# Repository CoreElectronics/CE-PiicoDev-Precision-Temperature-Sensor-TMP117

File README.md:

# PiicoDev® Precision Temperature Sensor TMP117

This is the repo for the Core Electronics [PiicoDev Precision Temperature Sensor TMP117](https://core-electronics.com.au/catalog/product/view/sku/CE07502).

The PiicoDev Precision Temperature Sensor features a low-power, high precision TMP117 with 16-bit resolution and an accuracy of ±0.1°C (across -20°C to +50°C) with no calibration required. The full operating range is -55°C to +150°C.

- Small size, high accuracy
- PiicoDev connector, compatible with Qwiic and STEMMA QT (3.3V only)
- 2.54mm breakout for breadboarding/prototyping
- Manufactured and [supported](https://core-electronics.com.au/contacts/) in Australia by Core Electronics

**Technical Specifications:**

- 4 configurable I2C addresses. Default: 0x48
- Dimensions: 25.4x25.4mm
- Mounting Holes: 2x M2.5
- TMP117:
  - ±0.1°C from -20°C to +50°C
  - ±0.15°C from -40°C to +70°C
  - ±0.2°C from -40°C to +100°C
  - ±0.25°C from -55°C to +125°C
  - ±0.3°C from -55°C to +150°C
  - 0.0078°C resolution (1 LSB)

# License
This project is open source - please review the LICENSE.md file for further licensing information.

If you have any technical questions, or concerns about licensing, please contact technical support on the [Core Electronics forums](https://forum.core-electronics.com.au/).

# Attribution
The hardware design of this module is influenced by the design from [Sparkfun](https://github.com/sparkfun/SparkFun_High_Precision_Temperature_Sensor_TMP117_Qwiic).

*\"PiicoDev\" and the PiicoDev logo are trademarks of Core Electronics Pty Ltd.*

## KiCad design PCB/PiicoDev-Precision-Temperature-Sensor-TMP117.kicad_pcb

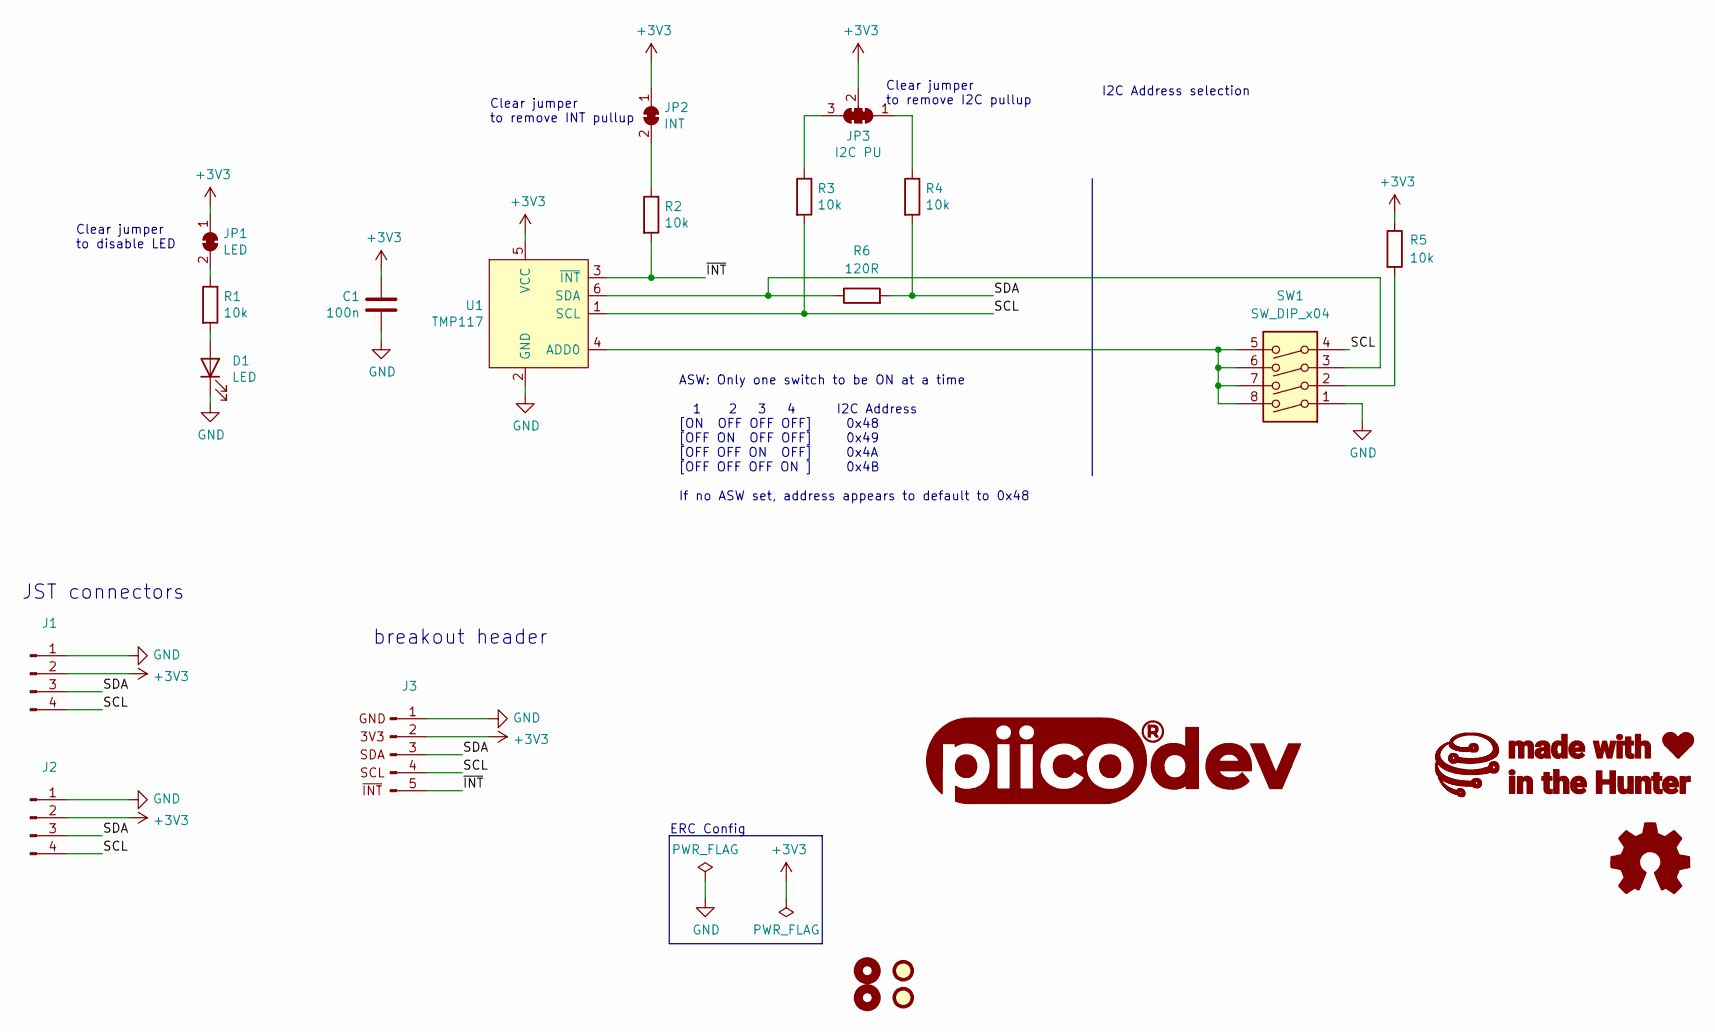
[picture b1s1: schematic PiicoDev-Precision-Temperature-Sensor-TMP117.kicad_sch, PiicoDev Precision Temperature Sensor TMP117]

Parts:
C1: 100n; C_0402_1005Metric
D1: LED; LED_0603_1608Metric
FID1, FID2: Fiducial; Fiducial_1mm_Mask2mm
G1: LOGO_CoreElectronics_no-text; CoreElectronics_logo_5mm
G2: LOGO_piico; piicodev_logo_14.2x3.4mm
G3: LOGO_made-with-love; piicodev_logo_14.2x3.4mm
H1, H4: MountingHole; MountingHole_2.7mm_M2.5
J1, J2: JST_SH_SM04B-SRSS-TB_1x04-1MP_P1.00mm_Horizontal
J3: PiicoDev_header_5pin_INT
JP1: LED; SolderJumper-2_P1.3mm_Bridged_RoundedPad1.0x1.5mm
JP2: INT; SolderJumper-2_P1.3mm_Bridged_RoundedPad1.0x1.5mm
JP3: I2C PU; SolderJumper-3_P1.3mm_Closed_RoundedPad1.0x1.5mm_NumberLabe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
LOGO1: Logo_Open_Hardware_Small; oshw
R1, R2, R3, R4, R5: 10k; R_0402_1005Metric
R6: 120R; R_0402_1005Metric
SW1: SW_DIP_x04; SW_DIP_x04_Slide_CHS-04A1
U1: TMP117; WSON-6-1EP_2x2mm_P0.65mm_EP1x1.6mm

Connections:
+3V3: C1.2, J1.2, J2.2, J3.2, JP1.1 (A), JP2.1 (A), JP3.2 (C), R5.1, U1.5 (VCC)
/SCL: J1.4, J2.4, J3.4, R3.2, SW1.4, U1.1 (SCL)
/SDA: J1.3, J2.3, J3.3, R4.2, R6.2
/~INT: J3.5, R2.2, U1.3 (~INT)
GND: C1.1, D1.1 (K), J1.1, J2.1, J3.1, SW1.1, U1.2 (GND)
unnamed: D1.2 (A), R1.2
unnamed: JP1.2 (B), R1.1
unnamed: JP2.2 (B), R2.1
unnamed: JP3.1 (A), R4.1
unnamed: JP3.3 (B), R3.1
unnamed: R5.2, SW1.2
unnamed: R6.1, SW1.3, U1.6 (SDA)
unnamed: SW1.5, SW1.6, SW1.7, SW1.8, U1.4 (ADD0)

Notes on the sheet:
JST connectors
Clear jumper to remove I2C pullup
ASW: Only one switch to be ON at a time 1 2 3 4 I2C Address [ON OFF OFF OFF] 0x48 [OFF ON OFF OFF] 0x49 [OFF OFF ON OFF] 0x4A [OFF OFF OFF ON ] 0x4B If no ASW set, address appears to default to 0x48
breakout header
ERC Config
I2C Address selection
Clear jumper to remove INT pullup
Clear jumper to disable LED

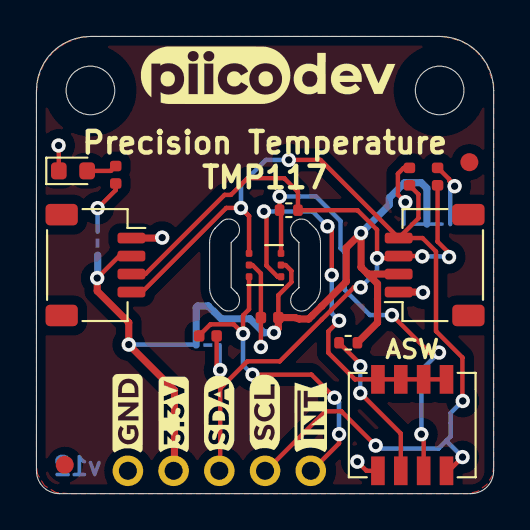
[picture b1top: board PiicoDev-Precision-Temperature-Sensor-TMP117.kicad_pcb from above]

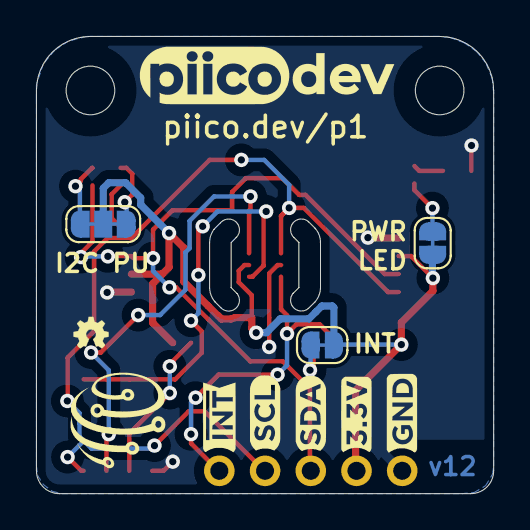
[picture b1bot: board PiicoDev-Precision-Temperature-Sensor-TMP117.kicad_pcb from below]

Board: 2 copper layers, 25.4 x 25.4 mm, 24 parts (7 on the bottom side), 13 nets.

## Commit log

2020-12-21 Update showcase-render.png
    Reduce filesize for politeness
2020-12-21 update readme formatting
2021-03-22 Update title blocks
2021-03-22 Add schematic pdf
2021-04-19 Fix link
2021-07-28 Update R1 to 4k7
    New LED is more efficient, use larger resistor. Optimise 1k out of the BOM
2021-12-30 v11 Update
    Change resistor values
    Add DIP switch and remove ADR jumper
    Update graphic labels
    Remove solder mask between jumper pads
    Update text formatting
2022-03-21 v12 Update
    Migrate to KiCad 6.0
    Add 120R resistor
    Add 4-bit DIP SW
2022-03-24 Tweak thermal holes
2022-04-19 add v12 comments, update schematic pdf
2023-01-08 annotate

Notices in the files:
PCB/PiicoDev-Precision-Temperature-Sensor-TMP117.kicad_pcb:
License: CCASAv4.0 http://creativecommons.org/licenses/by-sa/4.0
